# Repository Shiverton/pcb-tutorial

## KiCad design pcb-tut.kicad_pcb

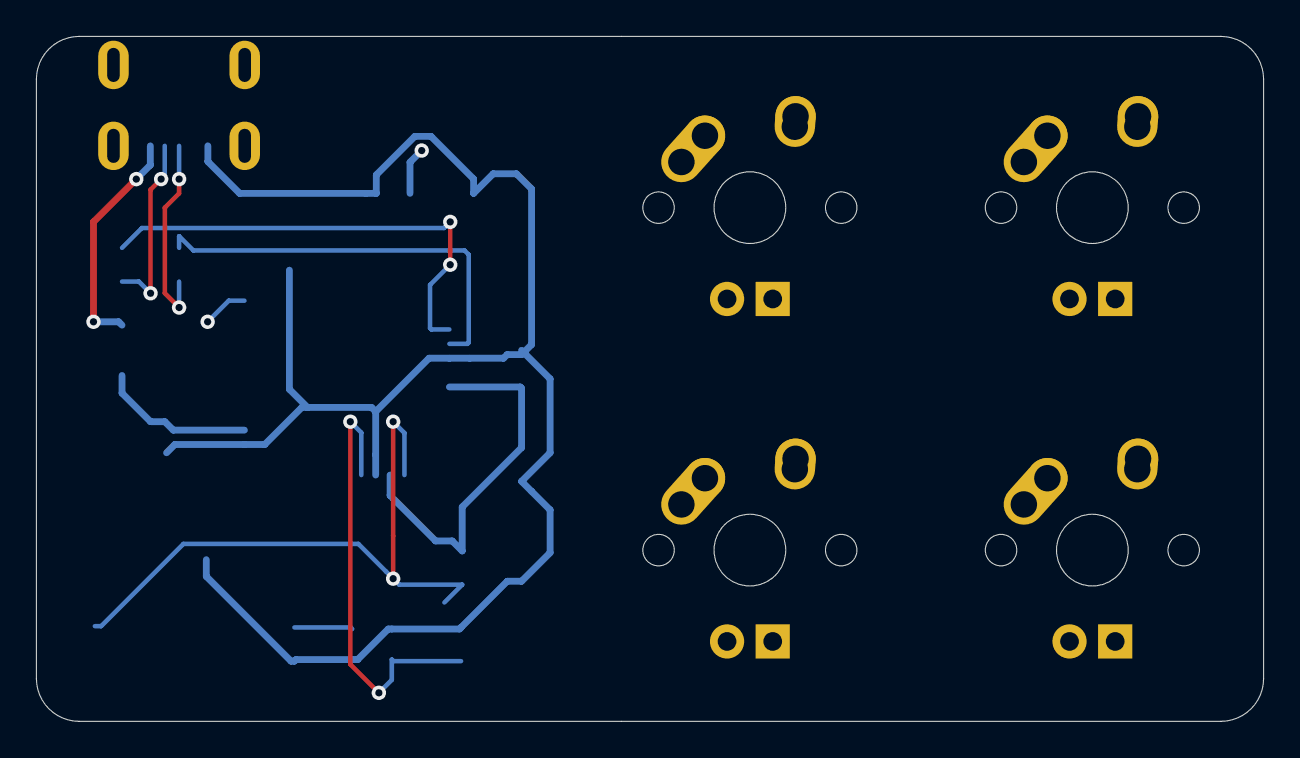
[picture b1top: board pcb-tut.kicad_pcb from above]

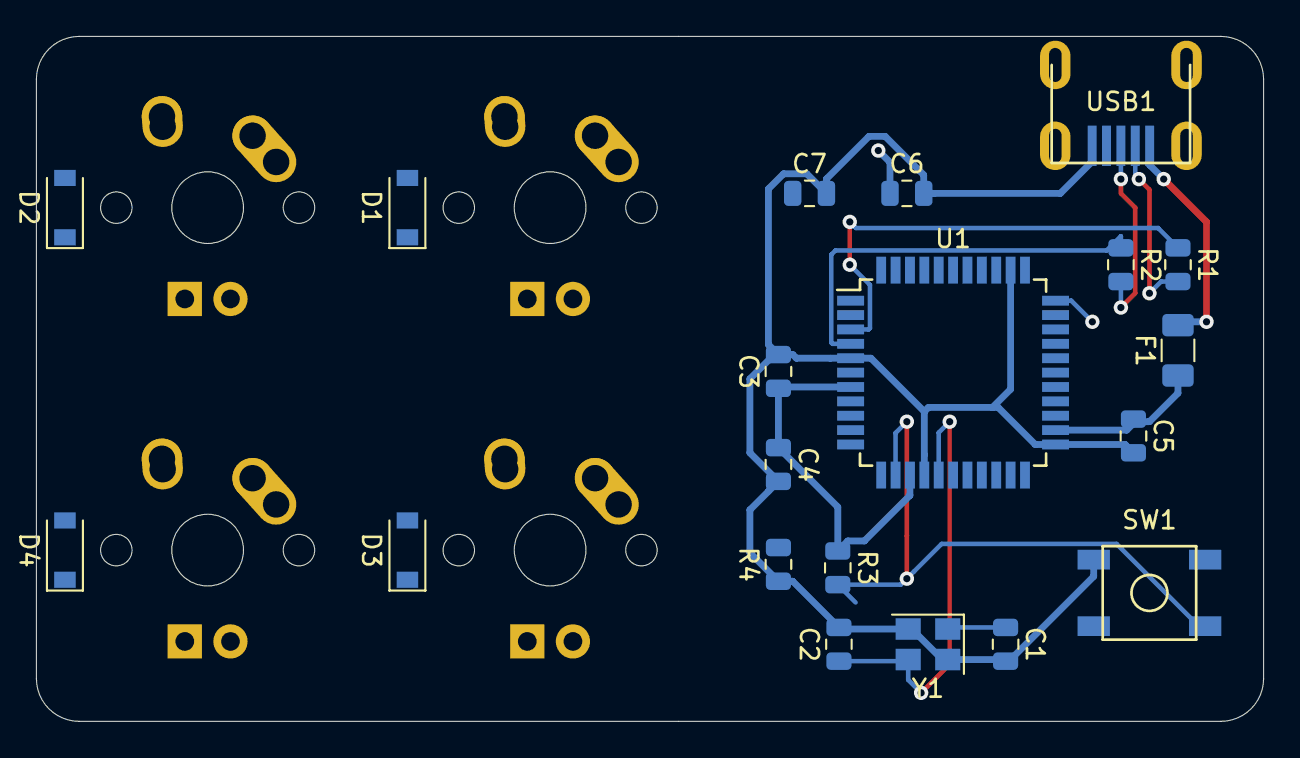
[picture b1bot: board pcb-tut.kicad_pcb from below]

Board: 2 copper layers, 68.3 x 38.1 mm, 24 parts (20 on the bottom side), 20 nets.

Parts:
C1, C2: 22pF; C_0805_2012Metric
C3: 1uF; C_0805_2012Metric
C4, C5, C7: 0.1uF; C_0805_2012Metric
C6: 10uF; C_0805_2012Metric
D1, D2, D3, D4: SOD-123; D_SOD-123
F1: 500mA; Fuse_1206_3216Metric
MX1, MX2, MX3, MX4: MX-1U
R1, R2: 22; R_0805_2012Metric
R3, R4: 10k; R_0805_2012Metric
SW1: SW_Push; SKQG-1155865
U1: ATmega32U4-AU; TQFP-44_10x10mm_P0.8mm
USB1: Molex-0548190589
Y1: 16MHz; Crystal_SMD_3225-4Pin_3.2x2.5mm

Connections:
+5V: C3.1, C4.1, C5.1, C6.1, F1.1, R3.1, U1.2, U1.7, U1.14, U1.24, U1.34, U1.44
COL0: MX1.1, MX2.1
COL1: MX3.1, MX4.1
D+: R2.2, USB1.3
D-: R1.2, USB1.4
GND: C1.2, C2.2, C3.2, C4.2, C5.2, C6.2, C7.2, R4.1, SW1.1, U1.5, U1.15, U1.23, U1.35, U1.43, USB1.1, Y1.2, Y1.4
unnamed: C1.1, U1.17, Y1.1
unnamed: C2.1, U1.16, Y1.3
unnamed: C7.1, U1.6
unnamed: D1.2, MX1.2
unnamed: D2.2, MX2.2
unnamed: D3.2, MX3.2
unnamed: D4.2, MX4.2
unnamed: R1.1, U1.3
unnamed: R2.1, U1.4
unnamed: R3.2, SW1.2, U1.13
unnamed: R4.2, U1.33
ROW0: D1.1, D3.1
ROW1: D2.1, D4.1
VCC: F1.2, USB1.5

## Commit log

2019-05-23 Initialize Project
2019-05-23 Add submodules
2019-05-23 Add footprint libraries
2019-05-23 Sch and footprint data
